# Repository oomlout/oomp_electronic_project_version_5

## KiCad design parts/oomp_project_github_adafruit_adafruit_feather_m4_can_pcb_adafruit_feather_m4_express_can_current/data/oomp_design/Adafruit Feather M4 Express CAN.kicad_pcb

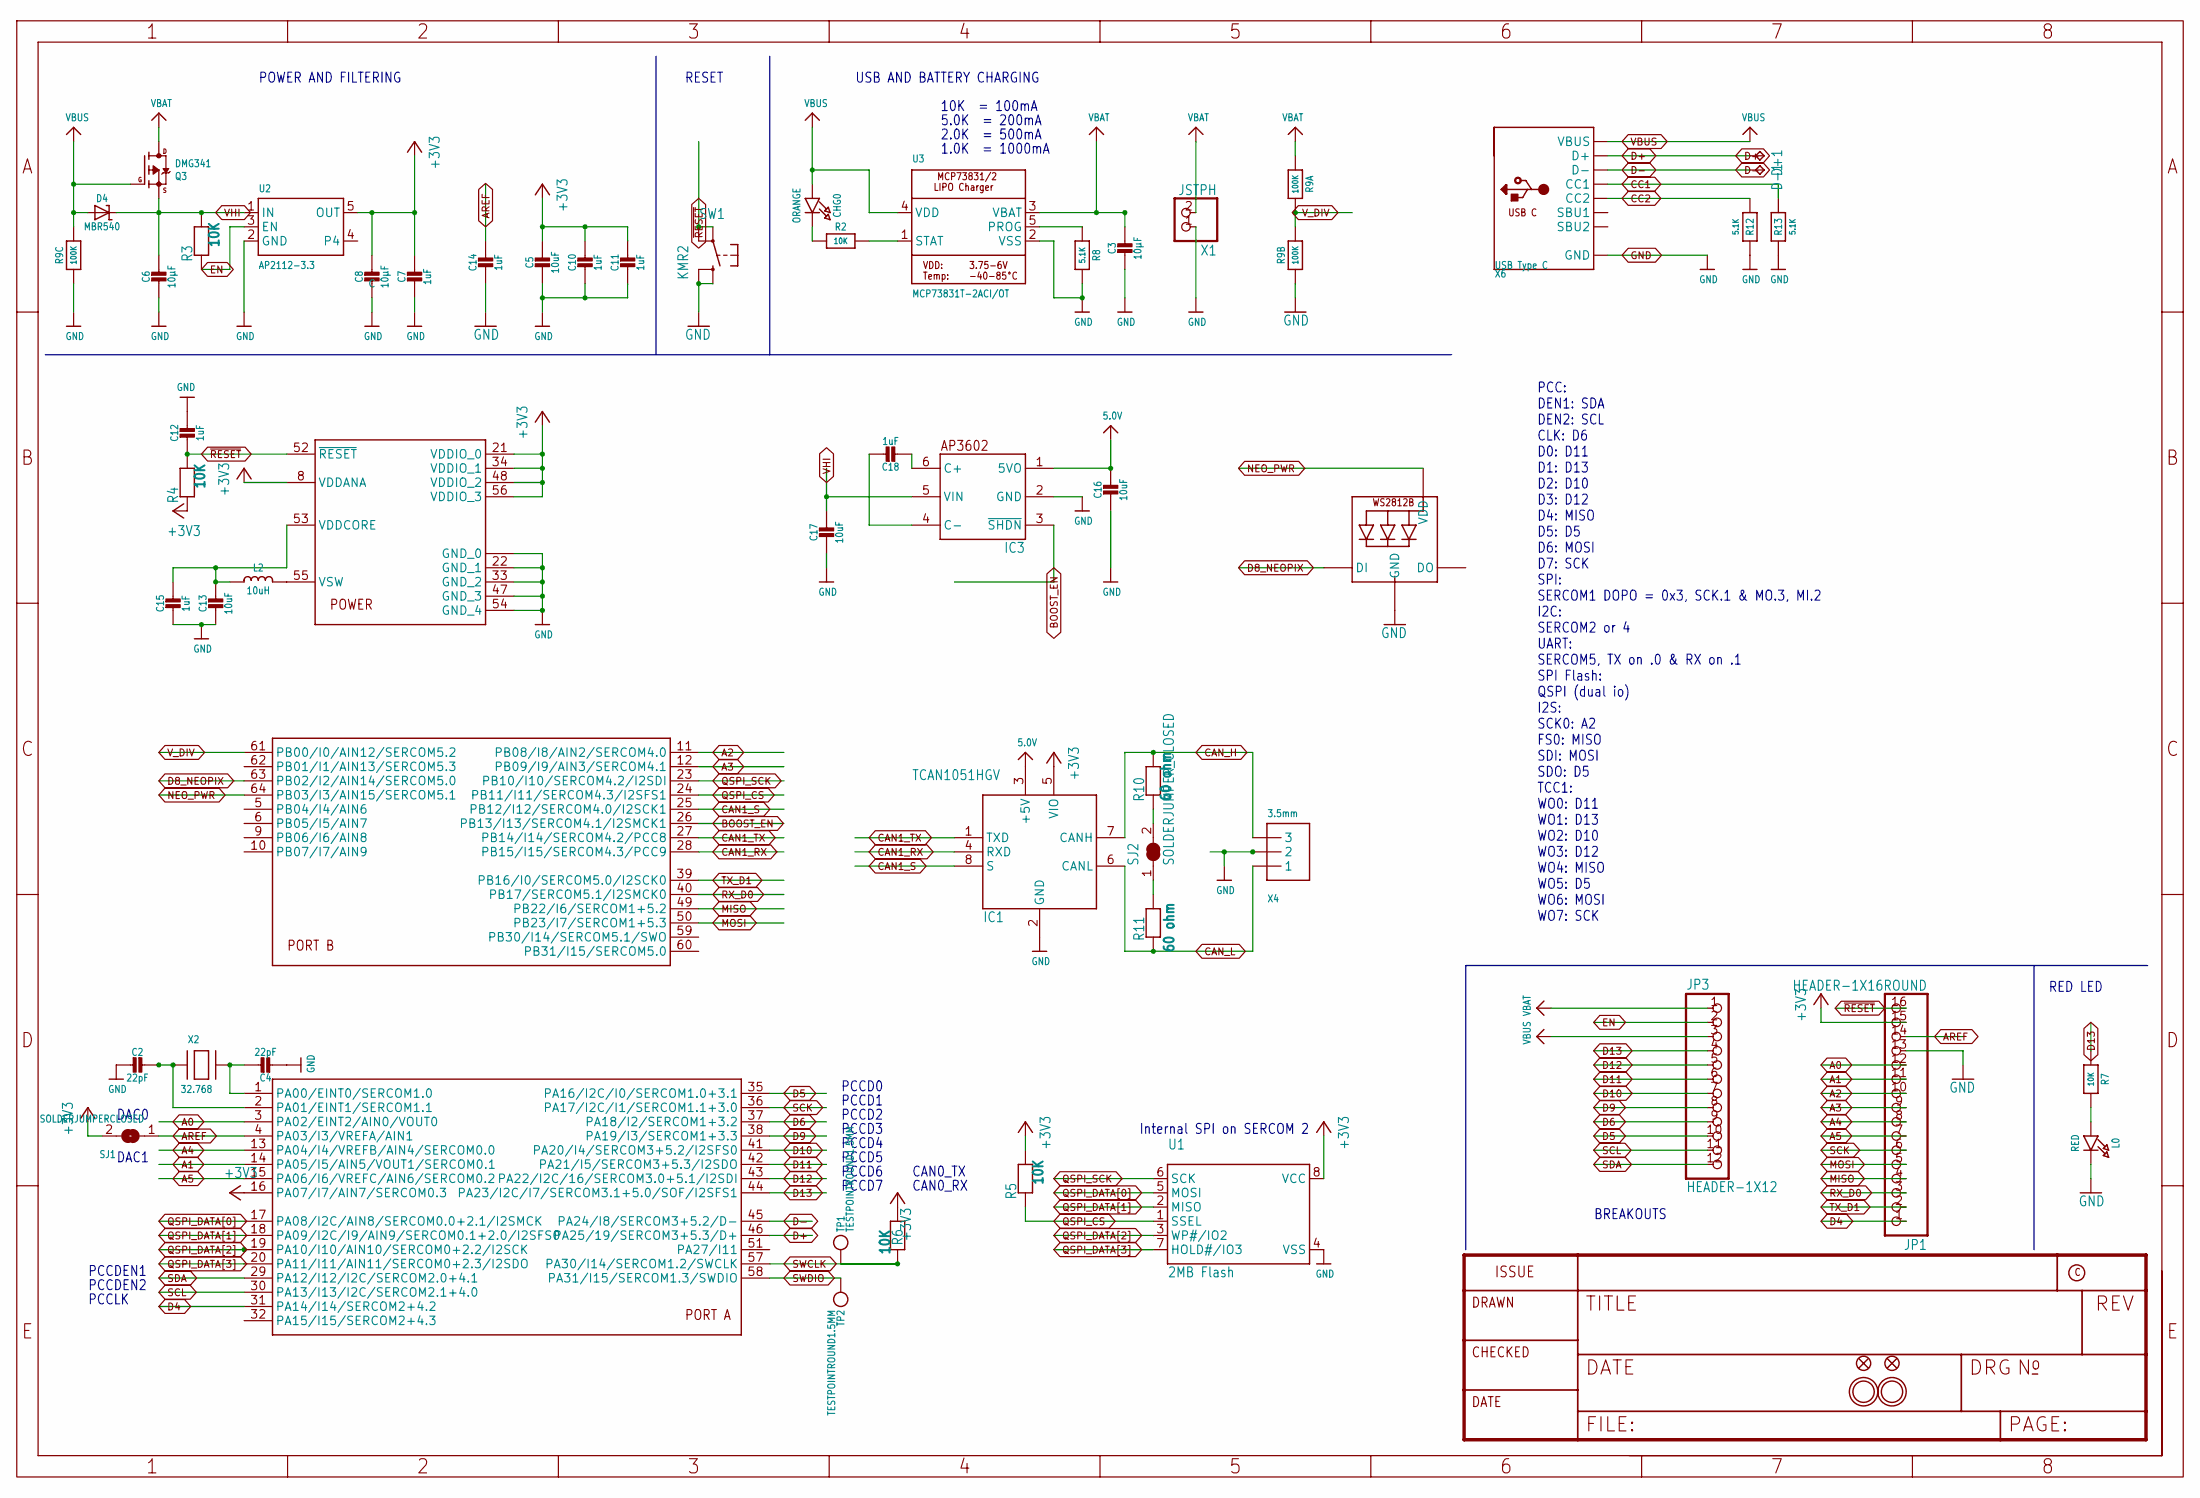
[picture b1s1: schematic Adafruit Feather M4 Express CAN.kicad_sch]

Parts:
C2, C4: 22pF; 0603-NO
C3, C6, C8: 10µF; 0805-NO
C5, C13, C17: 10uF; 0805-NO
C7, C10, C11, C12, C14, C15: 1uF; 0603-NO
C16: 10uF; _0805MP
C18: 1uF; 0805_10MGAP
CHG0: ORANGE; CHIPLED_0603_NOOUTLINE
D4: MBR540; SOD-123
D+1: TPB1,27; B1,27
D-1: TPB1,27; B1,27
IC1: TCAN1051HGV; SOIC8_150MIL
IC3: AP3602; SOT23-6
JP1: HEADER-1X16ROUND; 1X16_ROUND
JP3: HEADER-1X12; 1X12_ROUND
L0: RED; CHIPLED_0603_NOOUTLINE
L2: 10uH; INDUCTOR_1007
LED1: WS2812B3535; LED3535
Q3: DMG341; SOT23-R
R2, R3, R4, R5, R6, R7: 10K; 0603-NO
R8, R12, R13: 5.1K; 0603-NO
R9: 100K; RESPACK_4X0603_NO
R10, R11: 60 ohm; 0805-NO
SJ1: SOLDERJUMPERCLOSED; SOLDERJUMPER_CLOSEDWIRE
SJ2: SOLDERJUMPER_CLOSED; SOLDERJUMPER_CLOSEDWIRE
SW1: KMR2; BTN_KMR2_4.6X2.8
TP1, TP2: TESTPOINTROUND1.5MM; TESTPOINT_ROUND_1.5MM
U1: 2MB Flash; USON8
U2: AP2112-3.3; SOT23-5@1
U3: MCP73831T-2ACI/OT; SOT23-5
U$14: ATSAMD51J; PQFN64-1
U$31, U$32: MOUNTINGHOLE2.5; MOUNTINGHOLE_2.5_PLATED
U$34, U$35: FIDUCIAL_1MM
X1: JSTPH; JSTPH2_BATT
X2: 32.768; XTAL3215
X4: 3.5mm; TERMBLOCK_1X3-3.5MM
X6: USB Type C; USB_C_CUSB31-CFM2AX-01-X

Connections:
5.0V: C16.1, IC1.3 (+5V), IC3.1 (5VO)
+3V3: C5.1, C7.1, C8.1, C10.1, C11.1, IC1.5 (VIO), JP1.15, R4.1, R5.2, R6.1, SJ1.2, U1.8 (VCC), U2.5 (OUT), U$14.8 (VDDANA), U$14.16 (PA07/I7/AIN7/SERCOM0.3), U$14.21 (VDDIO_0), U$14.34 (VDDIO_1), U$14.48 (VDDIO_2), U$14.56 (VDDIO_3)
A0: JP1.12, U$14.3 (PA02/EINT2/AIN0/VOUT0)
A1: JP1.11, U$14.14 (PA05/I5/AIN5/VOUT1/SERCOM0.1)
A2: JP1.10, U$14.11 (PB08/I8/AIN2/SERCOM4.0)
A3: JP1.9, U$14.12 (PB09/I9/AIN3/SERCOM4.1)
A4: JP1.8, U$14.13 (PA04/I4/VREFB/AIN4/SERCOM0.0)
A5: JP1.7, U$14.15 (PA06/I6/VREFC/AIN6/SERCOM0.2)
AREF: C14.1, JP1.14, SJ1.1, U$14.4 (PA03/I3/VREFA/AIN1)
BOOST_EN: IC3.3 (~SHDN), U$14.26 (PB13/I13/SERCOM4.1/I2SMCK1)
CAN1_RX: IC1.4 (RXD), U$14.28 (PB15/I15/SERCOM4.3/PCC9)
CAN1_S: IC1.8 (S), U$14.25 (PB12/I12/SERCOM4.0/I2SCK1)
CAN1_TX: IC1.1 (TXD), U$14.27 (PB14/I14/SERCOM4.2/PCC8)
CAN_H: IC1.7 (CANH), R10.2, X4.3
CAN_L: IC1.6 (CANL), R11.2, X4.1
CC1: R13.2, X6.A5 (CC1)
CC2: R12.2, X6.B5 (CC2)
D4: JP1.1, U$14.31 (PA14/I14/SERCOM2+4.2)
D5: JP3.10, U$14.35 (PA16/I2C/I0/SERCOM1.0+3.1)
D6: JP3.9, U$14.37 (PA18/I2/SERCOM1+3.2)
D8_NEOPIX: LED1.1 (DI), U$14.63 (PB02/I2/AIN14/SERCOM5.0)
D9: JP3.8, U$14.38 (PA19/I3/SERCOM1+3.3)
D10: JP3.7, U$14.41 (PA20/I4/SERCOM3+5.2/I2SFS0)
D11: JP3.6, U$14.42 (PA21/I5/SERCOM3+5.3/I2SDO)
D12: JP3.5, U$14.43 (PA22/I2C/16/SERCOM3.0+5.1/I2SDI)
D13: JP3.4, R7.1, U$14.44 (PA23/I2C/I7/SERCOM3.1+5.0/SOF/I2SFS1)
D+: D+1.TP, U$14.46 (PA25/19/SERCOM3+5.3/D+), X6.A6 (D+), X6.B6 (D+)
D-: D-1.TP, U$14.45 (PA24/I8/SERCOM3+5.2/D-), X6.A7 (D-), X6.B7 (D-)
EN: JP3.2, R3.1, U2.3 (EN)
GND: C2.2, C3.2, C4.2, C5.2, C6.2, C7.2, C8.2, C10.2, C11.2, C12.1, C13.2, C14.2, C15.2, C16.2, C17.2, IC1.2 (GND), IC3.2 (GND), JP1.13, L0.C, LED1.4 (GND), R8.2, R9.3 (1), R9.7 (2), R12.1, R13.1, SW1.B (S), SW1.B' (S1), U1.4 (VSS), U2.2 (GND), U3.2 (VSS), U$14.7 (GND_0), U$14.22 (GND_1), U$14.33 (GND_2), U$14.47 (GND_3), U$14.54 (GND_4), U$14.EXP (GND_0), X1.1, X4.2, X6.A1B12 (GND), X6.B1A12 (GND)
MISO: JP1.4, U$14.49 (PB22/I6/SERCOM1+5.2)
MOSI: JP1.5, U$14.50 (PB23/I7/SERCOM1+5.3)
unnamed: CHG0.C, R2.1
unnamed: L0.A, R7.2
unnamed: R2.2, U3.1 (STAT)
unnamed: R8.1, U3.5 (PROG)
unnamed: R10.1, SJ2.2
unnamed: C4.1, U$14.1 (PA00/EINT0/SERCOM1.0), X2.P$2
unnamed: C18.2, IC3.6 (C+)
unnamed: C18.1, IC3.4 (C-)
unnamed: C2.1, U$14.2 (PA01/EINT1/SERCOM1.1), X2.P$1
unnamed: L2.P$2 (2), U$14.55 (VSW)
unnamed: R11.1, SJ2.1
NEO_PWR: LED1.2 (VDD), U$14.64 (PB03/I3/AIN15/SERCOM5.1)
QSPI_CS: R5.1, U1.1 (SSEL), U$14.24 (PB11/I11/SERCOM4.3/I2SFS1)
QSPI_DATA[0]: U1.5 (MOSI), U$14.17 (PA08/I2C/AIN8/SERCOM0.0+2.1/I2SMCK)
QSPI_DATA[1]: U1.2 (MISO), U$14.18 (PA09/I2C/I9/AIN9/SERCOM0.1+2.0/I2SFS0)
QSPI_DATA[2]: U1.3 (WP#/IO2), U$14.19 (PA10/I10/AIN10/SERCOM0+2.2/I2SCK)
QSPI_DATA[3]: U1.7 (HOLD#/IO3), U$14.20 (PA11/I11/AIN11/SERCOM0+2.3/I2SDO)
QSPI_SCK: U1.6 (SCK), U$14.23 (PB10/I10/SERCOM4.2/I2SDI)
RX_D0: JP1.3, U$14.40 (PB17/SERCOM5.1/I2SMCK0)
SCK: JP1.6, U$14.36 (PA17/I2C/I1/SERCOM1.1+3.0)
SCL: JP3.11, U$14.30 (PA13/I13/I2C/SERCOM2.1+4.0)
SDA: JP3.12, U$14.29 (PA12/I12/I2C/SERCOM2.0+4.1)
SWCLK: R6.2, TP1.P$1, U$14.57 (PA30/I14/SERCOM1.2/SWCLK)
SWDIO: TP2.P$1, U$14.58 (PA31/I15/SERCOM1.3/SWDIO)
TX_D1: JP1.2, U$14.39 (PB16/I0/SERCOM5.0/I2SCK0)
VBAT: C3.1, JP3.1, Q3.3 (D), R9.8 (2), U3.3 (VBAT), X1.2
VBUS: CHG0.A, D4.A, JP3.3, Q3.1 (G), R9.6 (2), U3.4 (VDD), X6.A4B9 (VBUS), X6.B4A9 (VBUS)
VDDCORE1: C13.1, C15.1, L2.P$1 (1), U$14.53 (VDDCORE)
VHI: C6.1, C17.1, D4.C, IC3.5 (VIN), Q3.2 (S), R3.2, U2.1 (IN)
V_DIV: R9.1, R9.2 (1), U$14.61 (PB00/I0/AIN12/SERCOM5.2)
~RESET: C12.2, JP1.16, R4.2, SW1.A, SW1.A' (P1), U$14.52 (~RESET)

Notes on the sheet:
Internal SPI on SERCOM 2
PCCD4
RED LED
USB AND BATTERY CHARGING
PCCD3
PCCD0
1.0K = 1000mA
CAN0_TX
PCCDEN2
2.0K = 500mA
PCCD6
BREAKOUTS
PCCD5
5.0K = 200mA
CAN0_RX
PCCD2
POWER AND FILTERING
DAC0
PCCD7
PCCDEN1
PCC: DEN1: SDA DEN2: SCL CLK: D6 D0: D11 D1: D13 D2: D10 D3: D12 D4: MISO D5: D5 D6: MOSI D7: SCK SPI: SERCOM1 DOPO = 0x3, SCK.1 & MO.3, MI.2 I2C: SERCOM2 or 4 UART: SERCOM5, TX on .0 & RX on .1 SPI Flash: QSPI (dual io) I2S: SCK0: A2 FS0: MISO SDI: MOSI SDO: D5 TCC1: WO0: D11 WO1: D13 WO2: D10 WO3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
10K = 100mA
PCCLK
DAC1
RESET
PCCD1

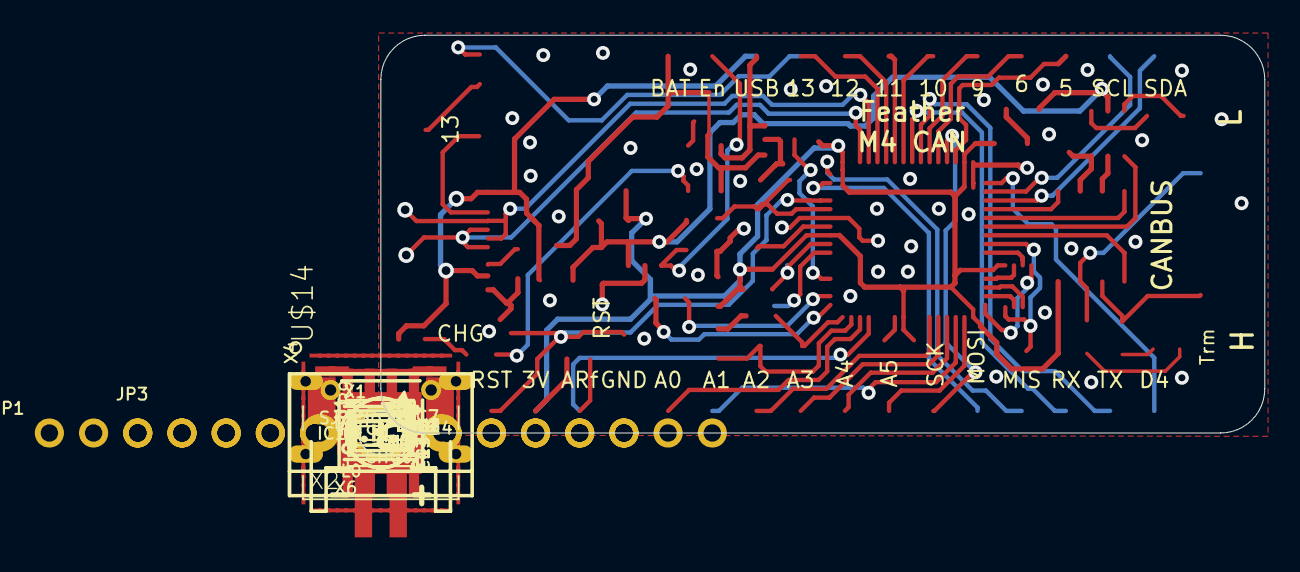
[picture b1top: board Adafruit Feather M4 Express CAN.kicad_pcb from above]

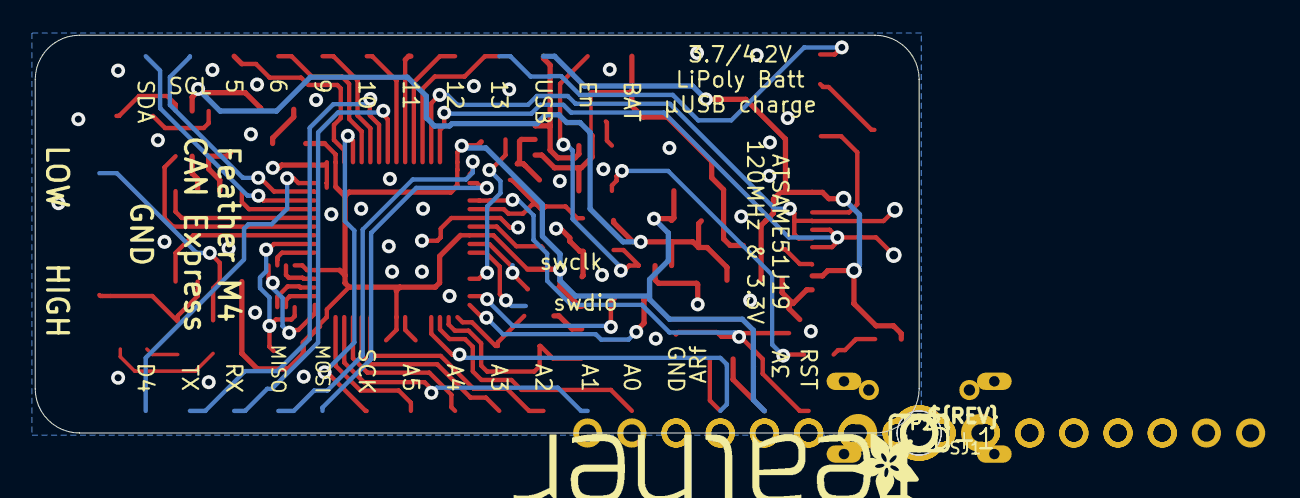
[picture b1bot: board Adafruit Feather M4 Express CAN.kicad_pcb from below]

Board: 2 copper layers, 50.8 x 22.9 mm, 63 parts (8 on the bottom side), 63 nets.

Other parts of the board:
U$1: ADAFRUIT_2.5MM
U$9: FEATHERLOGO
U$12: ADAFRUIT_3.5MM
U$13: PCBFEAT-REV-040
UNK_HOLE_0: dummyfp0
UNK_HOLE_1: dummyfp1

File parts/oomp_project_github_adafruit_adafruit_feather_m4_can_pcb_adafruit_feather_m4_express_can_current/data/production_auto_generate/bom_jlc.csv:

Comment,Designator,Footprint,LCSC Part #
,JP3,Adafruit Feather M4 Express CAN-import-fps:1X12_ROUND,C7501588
,JP1,Adafruit Feather M4 Express CAN-import-fps:1X16_ROUND,C7501270
,U$1,Adafruit Feather M4 Express CAN-import-fps:ADAFRUIT_2.5MM,
,U$12,Adafruit Feather M4 Express CAN-import-fps:ADAFRUIT_3.5MM,
,U$9,Adafruit Feather M4 Express CAN-import-fps:FEATHERLOGO,
,U$13,Adafruit Feather M4 Express CAN-import-fps:PCBFEAT-REV-040,
,"TP1,TP2",Adafruit Feather M4 Express CAN-import-fps:TESTPOINT_ROUND_1.5MM,
100K,R9,Adafruit Feather M4 Express CAN-import-fps:RESPACK_4X0603_NO,C25803
10K,"R2,R3,R4,R5,R6,R7",Adafruit Feather M4 Express CAN-import-fps:0603-NO,C98220
10uF,"C5,C13,C17",Adafruit Feather M4 Express CAN-import-fps:0805-NO,
10uF,C16,Adafruit Feather M4 Express CAN-import-fps:_0805MP,
10uH,L2,Adafruit Feather M4 Express CAN-import-fps:INDUCTOR_1007,
10µF,"C3,C6,C8",Adafruit Feather M4 Express CAN-import-fps:0805-NO,
1uF,"C7,C10,C11,C12,C14,C15",Adafruit Feather M4 Express CAN-import-fps:0603-NO,C5673
1uF,C18,Adafruit Feather M4 Express CAN-import-fps:0805_10MGAP,
22pF,"C2,C4",Adafruit Feather M4 Express CAN-import-fps:0603-NO,C105620
2MB Flash,U1,Adafruit Feather M4 Express CAN-import-fps:USON8,
3.5mm,X4,Adafruit Feather M4 Express CAN-import-fps:TERMBLOCK_1X3-3.5MM,
32.768,X2,Adafruit Feather M4 Express CAN-import-fps:XTAL3215,
5.1K,"R8,R12,R13",Adafruit Feather M4 Express CAN-import-fps:0603-NO,C23186
60 ohm,"R10,R11",Adafruit Feather M4 Express CAN-import-fps:0805-NO,
AP2112-3.3,U2,Adafruit Feather M4 Express CAN-import-fps:SOT23-5@1,
AP3602,IC3,Adafruit Feather M4 Express CAN-import-fps:SOT23-6,
ATSAMD51J,U$14,Adafruit Feather M4 Express CAN-import-fps:PQFN64-1,
DMG341,Q3,Adafruit Feather M4 Express CAN-import-fps:SOT23-R,
FIDUCIAL_1MM,"U$34,U$35",Adafruit Feather M4 Express CAN-import-fps:FIDUCIAL_1MM,
JSTPH,X1,Adafruit Feather M4 Express CAN-import-fps:JSTPH2_BATT,
KMR2,SW1,Adafruit Feather M4 Express CAN-import-fps:BTN_KMR2_4.6X2.8,
MBR540,D4,Adafruit Feather M4 Express CAN-import-fps:SOD-123,
MCP73831T-2ACI/OT,U3,Adafruit Feather M4 Express CAN-import-fps:SOT23-5,
ORANGE,CHG0,Adafruit Feather M4 Express CAN-import-fps:CHIPLED_0603_NOOUTLINE,
RED,L0,Adafruit Feather M4 Express CAN-import-fps:CHIPLED_0603_NOOUTLINE,
TCAN1051HGV,IC1,Adafruit Feather M4 Express CAN-import-fps:SOIC8_150MIL,
"TPB1,27","D+1,D-1","Adafruit Feather M4 Express CAN-import-fps:B1,27",
USB Type C,X6,Adafruit Feather M4 Express CAN-import-fps:USB_C_CUSB31-CFM2AX-01-X,
WS2812B3535,LED1,Adafruit Feather M4 Express CAN-import-fps:LED3535,

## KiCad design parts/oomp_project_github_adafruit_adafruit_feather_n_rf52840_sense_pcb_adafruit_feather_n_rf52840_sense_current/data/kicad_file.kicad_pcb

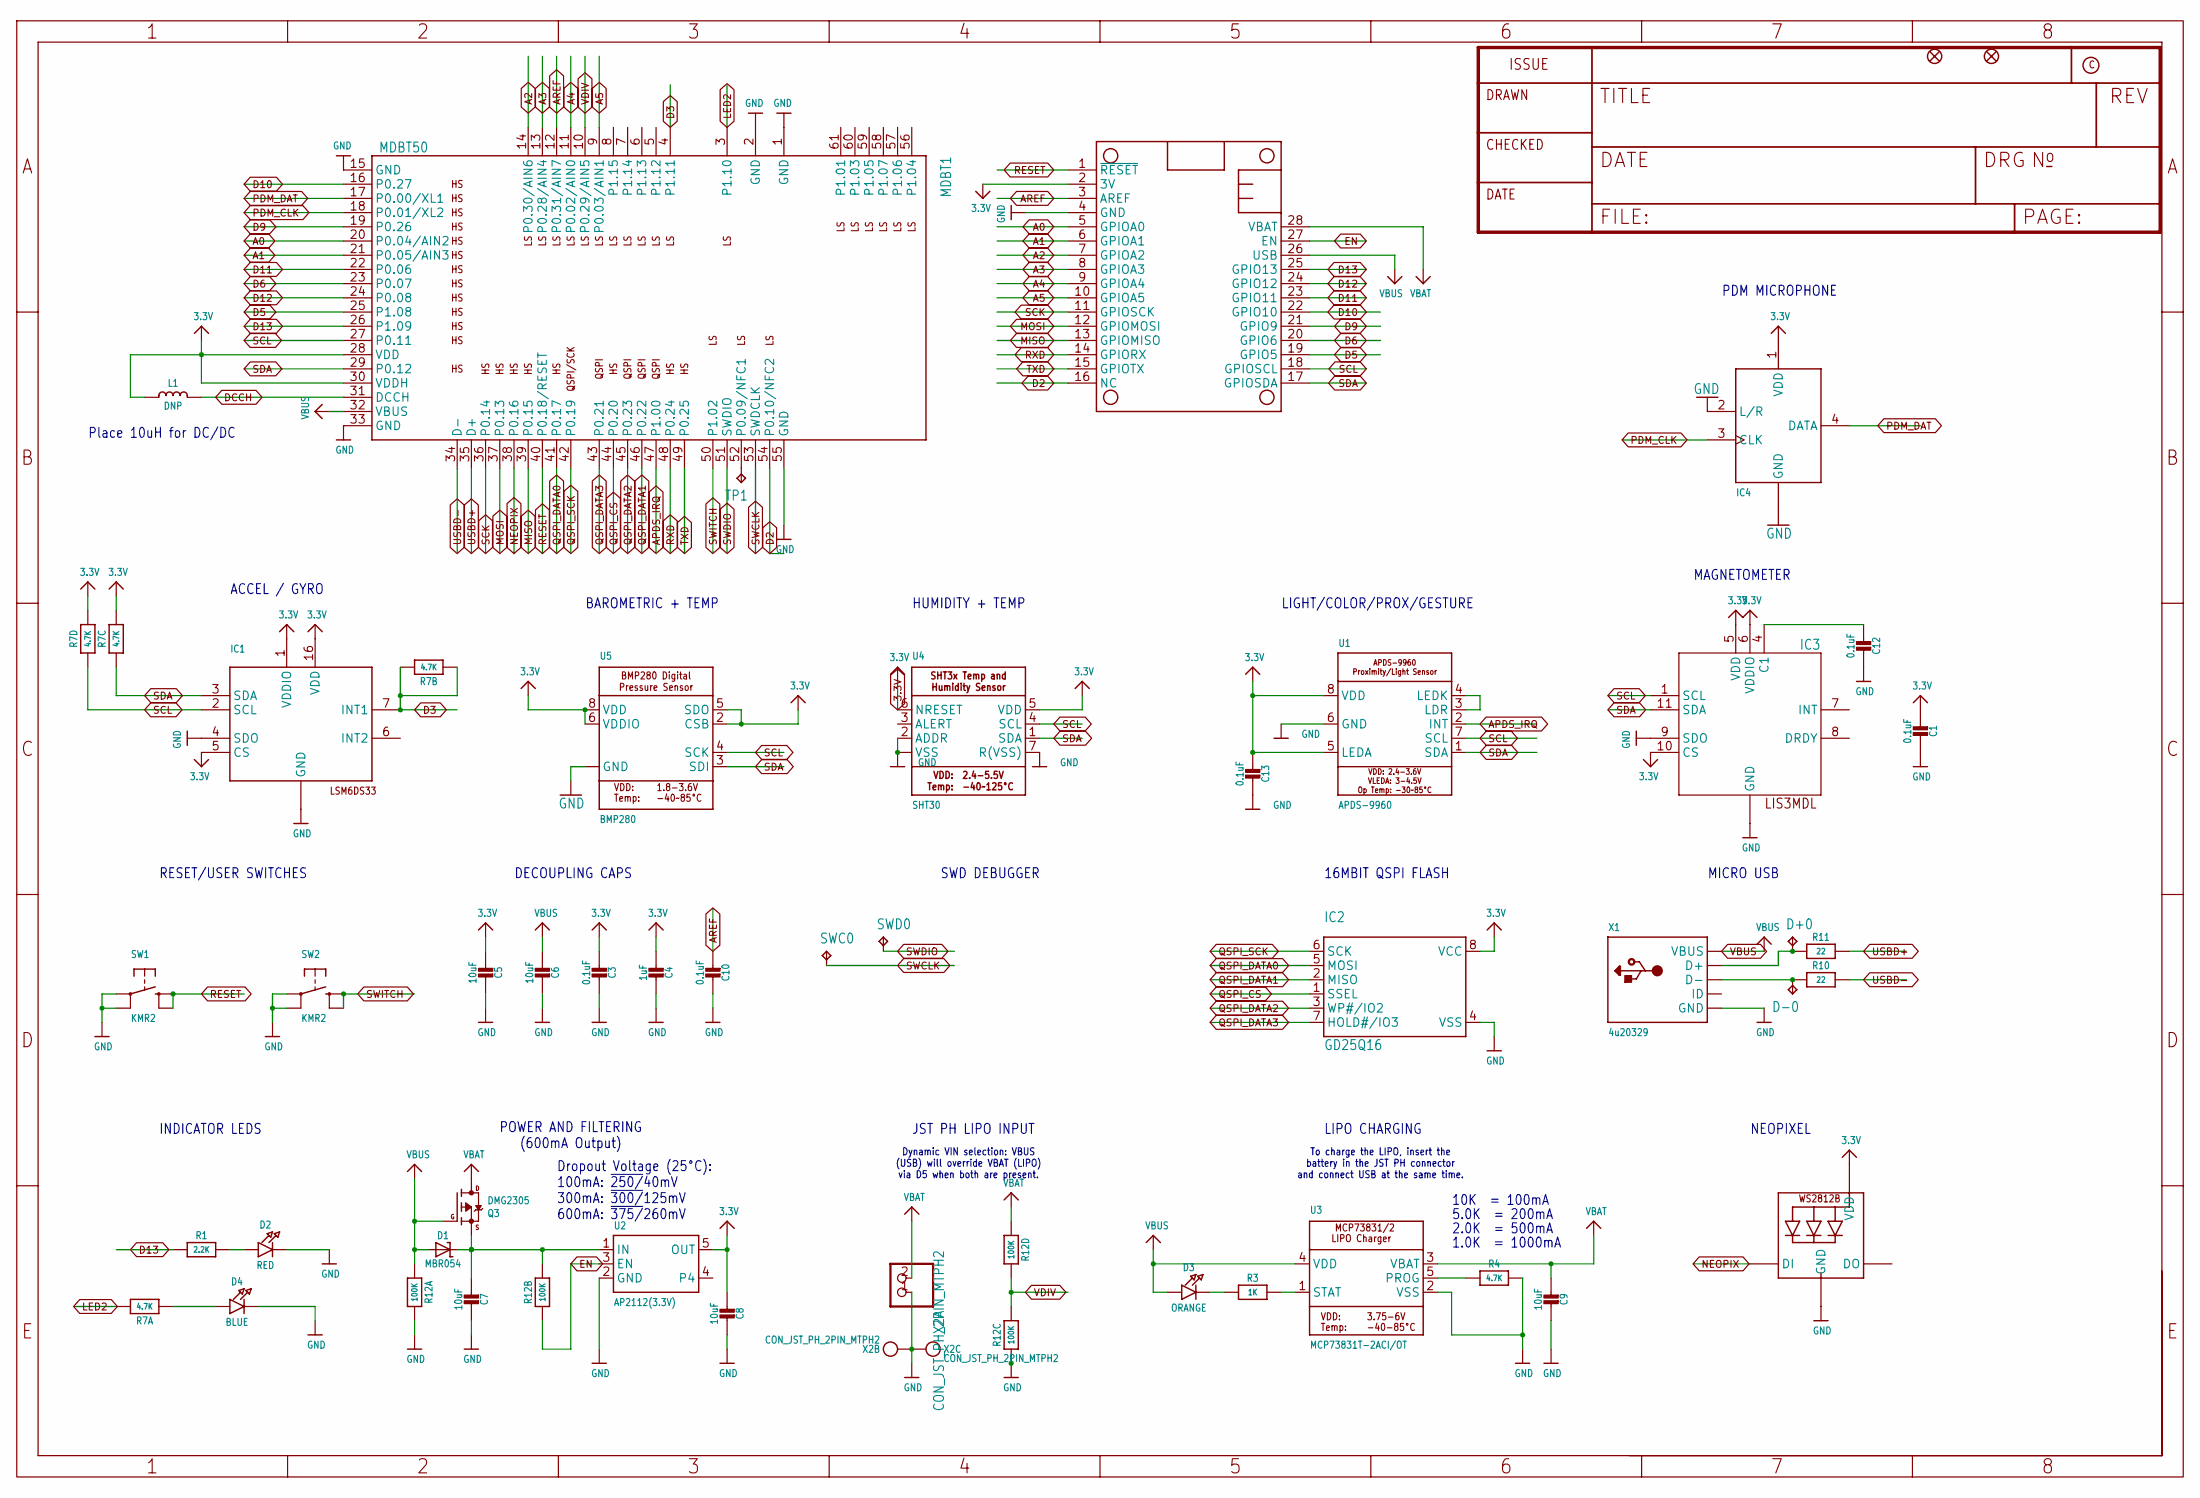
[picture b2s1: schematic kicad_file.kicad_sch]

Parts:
C1, C3, C10, C12, C13: 0.1uF; 0603-NO
C4: 1uF; 0603-NO
C5, C6, C7, C8, C9: 10uF; 0805-NO
D1: MBR054; SOD-123
D2: RED; CHIPLED_0805_NOOUTLINE
D3: ORANGE; CHIPLED_0805_NOOUTLINE
D4: BLUE; CHIPLED_0603_NOOUTLINE
D+0: TPTP10R; TP10R
D-0: TPTP10R; TP10R
FID1, FID2: FIDUCIAL_1MM
IC1: LSM6DS33; LGA16_3X3MM
IC2: GD25Q16; USON8
IC3: LIS3MDL; LGA12_2X2MM
IC4: MIC_PDM; SPK0415HM4H
L1: DNP; _0805MP
LED1: WS2812B3535; LED3535
MDBT1: MDBT50
MS1: FEATHERWING_NODIM
Q3: DMG2305; SOT23-R
R1: 2.2K; 0603-NO
R3: 1K; 0603-NO
R4: 4.7K; 0603-NO
R7: 4.7K; RESPACK_4X0603
R10, R11: 22; 0603-NO
R12: 100K; RESPACK_4X0603
SW1, SW2: KMR2; BTN_KMR2_4.6X2.8
SWC0: TPTP12R; TP12R
SWD0: TPTP12R; TP12R
TP1: TPTP10R; TP10R
U1: APDS-9960
U2: AP2112(3.3V); SOT23-5
U3: MCP73831T-2ACI/OT; SOT23-5
U4: SHT30; SHT3X
U5: BMP280
X1: 4u20329; 4UCONN_20329_V2
X2: CON_JST_PH_2PIN_MTPH2; JSTPH2

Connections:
3.3V: C1.2, C3.2, C4.2, C5.2, C8.2, C13.2, IC1.1 (VDDIO), IC1.5 (CS), IC1.16 (VDD), IC2.8 (VCC), IC3.5 (VDD), IC3.6 (VDDIO), IC3.10 (CS), IC4.1 (VDD), L1.1, LED1.2 (VDD), MDBT1.28 (VDD), MDBT1.30 (VDDH), MS1.2 (3V), R7.5 (2), R7.6 (2), U1.5 (LEDA), U1.8 (VDD), U2.5 (OUT), U4.5 (VDD), U4.6 (NRESET), U5.2 (CSB), U5.5 (SDO), U5.6 (VDDIO), U5.8 (VDD)
A0: MDBT1.20 (P0.04/AIN2), MS1.5 (GPIOA0)
A1: MDBT1.21 (P0.05/AIN3), MS1.6 (GPIOA1)
A2: MDBT1.14 (P0.30/AIN6), MS1.7 (GPIOA2)
A3: MDBT1.13 (P0.28/AIN4), MS1.8 (GPIOA3)
A4: MDBT1.11 (P0.02/AIN0), MS1.9 (GPIOA4)
A5: MDBT1.9 (P0.03/AIN1), MS1.10 (GPIOA5)
APDS_IRQ: MDBT1.47 (P1.00), U1.2 (INT)
AREF: C10.2, MDBT1.12 (P0.31/AIN7), MS1.3 (AREF)
CAP1: C12.2, IC3.4 (C1)
D2: MDBT1.54 (P0.10/NFC2), MS1.16 (NC)
D3: IC1.7 (INT1), MDBT1.4 (P1.11), R7.2 (1), R7.7 (2)
D5: MDBT1.25 (P1.08), MS1.19 (GPIO5)
D6: MDBT1.23 (P0.07), MS1.20 (GPIO6)
D9: MDBT1.19 (P0.26), MS1.21 (GPIO9)
D10: MDBT1.16 (P0.27), MS1.22 (GPIO10)
D11: MDBT1.22 (P0.06), MS1.23 (GPIO11)
D12: MDBT1.24 (P0.08), MS1.24 (GPIO12)
D13: MDBT1.26 (P1.09), MS1.25 (GPIO13), R1.1
D+: D+0.TP, R11.1, X1.D+
D-: D-0.TP, R10.1, X1.D-
DCCH: L1.2, MDBT1.31 (DCCH)
EN: MS1.27 (EN), R12.2 (1), U2.3 (EN)
GND: C1.1, C3.1, C4.1, C5.1, C6.1, C7.1, C8.1, C9.1, C10.1, C12.1, C13.1, D2.C, D4.C, IC1.4 (SDO), IC1.8 (GND), IC1.9 (GND), IC1.10 (GND), IC1.11 (GND), IC1.12 (GND), IC1.13 (GND), IC1.15 (GND), IC2.4 (VSS), IC3.2 (GND), IC3.3 (GND), IC3.9 (SDO), IC3.12 (GND), IC4.2 (L/R), IC4.5 (GND), IC4.6 (GND), IC4.7 (GND), IC4.8 (GND), LED1.4 (GND), MDBT1.1 (GND), MDBT1.2 (GND), MDBT1.15 (GND), MDBT1.33 (GND), MDBT1.55 (GND), MS1.4 (GND), R4.2, R12.3 (1), R12.8 (2), SW1.A, SW1.A' (P1), SW2.A, SW2.A' (P1), U1.6 (GND), U2.2 (GND), U3.2 (VSS), U4.2 (ADDR), U4.7 (R(VSS)), U4.8 (VSS), U4.THERMAL (VSS), U5.1 (GND), U5.7 (GND), X1.BASE@1 (GND), X1.BASE@2 (GND), X1.GND, X1.SPRT@1 (GND), X1.SPRT@2 (GND), X1.SPRT@3 (GND), X1.SPRT@4 (GND), X2.1, X2.NC1, X2.NC2
LED2: MDBT1.3 (P1.10), R7.8 (2)
MISO: MDBT1.39 (P0.15), MS1.13 (GPIOMISO)
MOSI: MDBT1.37 (P0.13), MS1.12 (GPIOMOSI)
unnamed: D3.C, R3.1
unnamed: U1.3 (LDR), U1.4 (LEDK)
unnamed: D4.A, R7.1
unnamed: D2.A, R1.2
unnamed: R3.2, U3.1 (STAT)
unnamed: R4.1, U3.5 (PROG)
NEOPIX: LED1.1 (DI), MDBT1.38 (P0.16)
NFC2: MDBT1.52 (P0.09/NFC1), TP1.TP
PDM_CLK: IC4.3 (CLK), MDBT1.18 (P0.01/XL2)
PDM_DAT: IC4.4 (DATA), MDBT1.17 (P0.00/XL1)
QSPI_CS: IC2.1 (SSEL), MDBT1.44 (P0.20)
QSPI_DATA0: IC2.5 (MOSI), MDBT1.41 (P0.17)
QSPI_DATA1: IC2.2 (MISO), MDBT1.46 (P0.22)
QSPI_DATA2: IC2.3 (WP#/IO2), MDBT1.45 (P0.23)
QSPI_DATA3: IC2.7 (HOLD#/IO3), MDBT1.43 (P0.21)
QSPI_SCK: IC2.6 (SCK), MDBT1.42 (P0.19)
RESET: MDBT1.40 (P0.18/RESET), MS1.1 (~RESET), SW1.B (S), SW1.B' (S1)
RXD: MDBT1.48 (P0.24), MS1.14 (GPIORX)
SCK: MDBT1.36 (P0.14), MS1.11 (GPIOSCK)
SCL: IC1.2 (SCL), IC3.1 (SCL), MDBT1.27 (P0.11), MS1.18 (GPIOSCL), R7.4 (1), U1.7 (SCL), U4.4 (SCL), U5.4 (SCK)
SDA: IC1.3 (SDA), IC3.11 (SDA), MDBT1.29 (P0.12), MS1.17 (GPIOSDA), R7.3 (1), U1.1 (SDA), U4.1 (SDA), U5.3 (SDI)
SWCLK: MDBT1.53 (SWDCLK), SWC0.TP
SWDIO: MDBT1.51 (SWDIO), SWD0.TP
SWITCH: MDBT1.50 (P1.02), SW2.B (S), SW2.B' (S1)
TXD: MDBT1.49 (P0.25), MS1.15 (GPIOTX)
USBD+: MDBT1.35 (D+), R11.2
USBD-: MDBT1.34 (D-), R10.2
VBAT: C9.2, MS1.28 (VBAT), Q3.3 (D), R12.4 (1), U3.3 (VBAT), X2.2
VBUS: C6.2, D1.A, D3.A, MDBT1.32 (VBUS), MS1.26 (USB), Q3.1 (G), R12.1, U3.4 (VDD), X1.VBUS
VDIV: MDBT1.10 (P0.29/AIN5), R12.5 (2), R12.6 (2)
VHI: C7.2, D1.C, Q3.2 (S), R12.7 (2), U2.1 (IN)

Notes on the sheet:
RESET/USER SWITCHES
JST PH LIPO INPUT
16MBIT QSPI FLASH
HUMIDITY + TEMP
To charge the LIPO, insert the battery in the JST PH connector and connect USB at the same time.
MAGNETOMETER
LIGHT/COLOR/PROX/GESTURE
DECOUPLING CAPS
MICRO USB
BAROMETRIC + TEMP
Dropout Voltage (25°C): 100mA: ~{250/}40mV 300mA: ~{300/}125mV 600mA: ~{375/}260mV
Place 10uH for DC/DC
LIPO CHARGING
INDICATOR LEDS
ACCEL / GYRO
POWER AND FILTERING (600mA Output)
Dynamic VIN selection: VBUS (USB) will override VBAT (LIPO) via D5 when both are present.
5.0K = 200mA
2.0K = 500mA
10K = 100mA
PDM MICROPHONE
SWD DEBUGGER
1.0K = 1000mA
NEOPIXEL

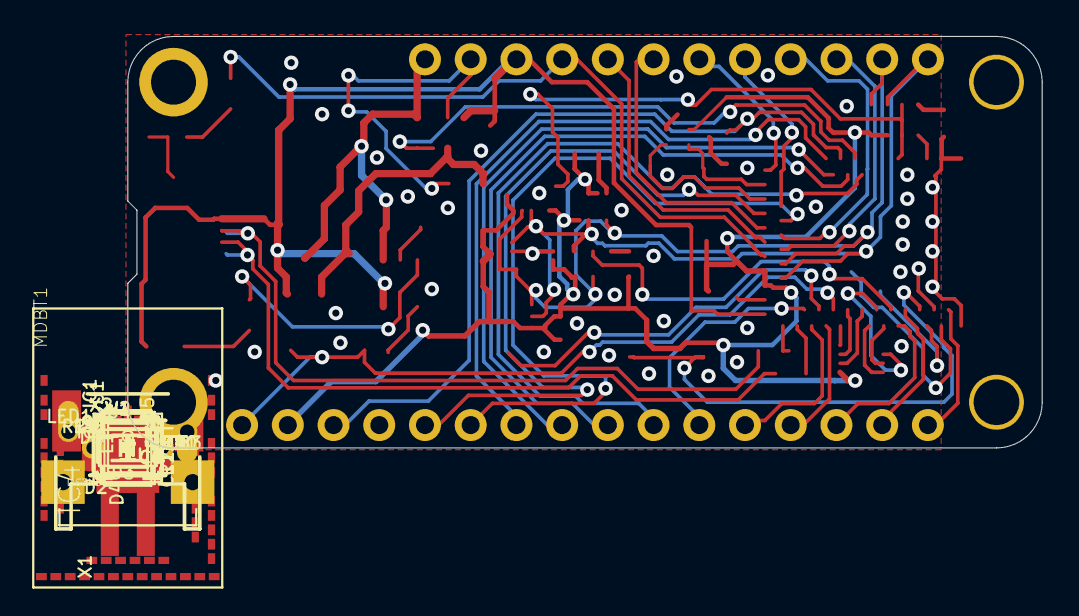
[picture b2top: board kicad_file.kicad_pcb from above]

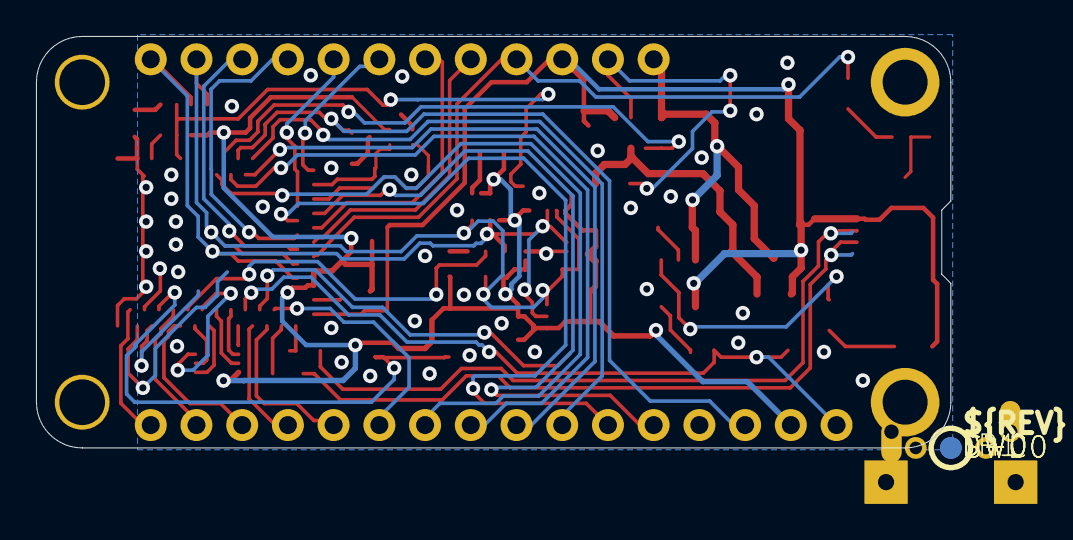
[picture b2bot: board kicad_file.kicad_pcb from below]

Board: 4 copper layers, 50.8 x 22.9 mm, 50 parts (7 on the bottom side), 58 nets.

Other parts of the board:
U$10: PCBFEAT-REV-056
U$14: FEATHERSENSE_TOP
U$75: FEATHERSENSE_BOT

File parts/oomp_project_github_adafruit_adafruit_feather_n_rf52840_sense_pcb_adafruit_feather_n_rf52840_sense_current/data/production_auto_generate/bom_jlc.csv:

Comment,Designator,Footprint,LCSC Part #
,U$75,Adafruit Feather nRF52840 Sense-import-fps:FEATHERSENSE_BOT,
,U$14,Adafruit Feather nRF52840 Sense-import-fps:FEATHERSENSE_TOP,
,U$10,Adafruit Feather nRF52840 Sense-import-fps:PCBFEAT-REV-056,
0.1uF,"C1,C3,C10,C12,C13",Adafruit Feather nRF52840 Sense-import-fps:0603-NO,C14663
100K,R12,Adafruit Feather nRF52840 Sense-import-fps:RESPACK_4X0603,C25803
10uF,"C5,C6,C7,C8,C9",Adafruit Feather nRF52840 Sense-import-fps:0805-NO,
1K,R3,Adafruit Feather nRF52840 Sense-import-fps:0603-NO,C2907002
1uF,C4,Adafruit Feather nRF52840 Sense-import-fps:0603-NO,C5673
2.2K,R1,Adafruit Feather nRF52840 Sense-import-fps:0603-NO,C4190
22,"R10,R11",Adafruit Feather nRF52840 Sense-import-fps:0603-NO,C23345
4.7K,R4,Adafruit Feather nRF52840 Sense-import-fps:0603-NO,C23162
4.7K,R7,Adafruit Feather nRF52840 Sense-import-fps:RESPACK_4X0603,C23162
4u20329,X1,Adafruit Feather nRF52840 Sense-import-fps:4UCONN_20329_V2,
AP2112(3.3V),U2,Adafruit Feather nRF52840 Sense-import-fps:SOT23-5,
APDS-9960,U1,Adafruit Feather nRF52840 Sense-import-fps:APDS-9960,
BLUE,D4,Adafruit Feather nRF52840 Sense-import-fps:CHIPLED_0603_NOOUTLINE,
BMP280,U5,Adafruit Feather nRF52840 Sense-import-fps:BMP280,
CON_JST_PH_2PIN_MTPH2,X2,Adafruit Feather nRF52840 Sense-import-fps:JSTPH2,
DMG2305,Q3,Adafruit Feather nRF52840 Sense-import-fps:SOT23-R,
DNP,L1,Adafruit Feather nRF52840 Sense-import-fps:_0805MP,
FEATHERWING_NODIM,MS1,Adafruit Feather nRF52840 Sense-import-fps:FEATHERWING_NODIM,
GD25Q16,IC2,Adafruit Feather nRF52840 Sense-import-fps:USON8,
KMR2,"SW1,SW2",Adafruit Feather nRF52840 Sense-import-fps:BTN_KMR2_4.6X2.8,
LIS3MDL,IC3,Adafruit Feather nRF52840 Sense-import-fps:LGA12_2X2MM,
LSM6DS33,IC1,Adafruit Feather nRF52840 Sense-import-fps:LGA16_3X3MM,
MBR054,D1,Adafruit Feather nRF52840 Sense-import-fps:SOD-123,
MCP73831T-2ACI/OT,U3,Adafruit Feather nRF52840 Sense-import-fps:SOT23-5,
MDBT50,MDBT1,Adafruit Feather nRF52840 Sense-import-fps:MDBT50,
MIC_PDM,IC4,Adafruit Feather nRF52840 Sense-import-fps:SPK0415HM4H,
ORANGE,D3,Adafruit Feather nRF52840 Sense-import-fps:CHIPLED_0805_NOOUTLINE,
RED,D2,Adafruit Feather nRF52840 Sense-import-fps:CHIPLED_0805_NOOUTLINE,
SHT30,U4,Adafruit Feather nRF52840 Sense-import-fps:SHT3X,
TPTP10R,"D+0,D-0,TP1",Adafruit Feather nRF52840 Sense-import-fps:TP10R,
TPTP12R,"SWC0,SWD0",Adafruit Feather nRF52840 Sense-import-fps:TP12R,
WS2812B3535,LED1,Adafruit Feather nRF52840 Sense-import-fps:LED3535,
